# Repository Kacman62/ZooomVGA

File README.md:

# ZooomVGA
An STM32 dev board complete with VGA out

# The Idea

I've been spending a lot of time on software recently and I wanted to do another hardware project. After browsing the Hack CLub slack, I saw there was a zoom call for Blueprint, the hardware program and I decided to join in. The theme was a Trace Race, where you try to make a board in the shortest amount of time. Just an hour before I saw a [VGA library](https://github.com/RoCorbera/BlueVGA) for the exact same STM32 module in the challenge and I knew what my proejct was going to be. The schematic was pretty quick to put together, using a USB C port, an ASM power regulator, the STM32F103C8, a Crystal Oscillator and the VGA port. After getting it reviewed by Kai, and improving it a little bit I moved onto the board in about an hour and a half. The board was a little harder, the VGA port is bigger than the width of a breadboard so I had to flange it out a little. But after aligning everything I started routing the pins. This was a lot harder, I put the MCU off center to get both the USB lines and the crystal to be close to it, but this caused the left side to be very cramped and a pain to route. After 2 hours of painful routing, and another half hour of polish, I finished the entire board in 4 hours. I decided on the name ZooomVGA because this is the fastest I've designed a project, and it was created mainly on the Zoom call.

# The rest of the Owl

I then created a Logo for the board, imporoved the silkscreen, added my logo and exported it to JLCPCB, coming in at around $15 with the stencil and shipping. 
While making the BOM i noticed a slight error with the VGA port, so I changed it to a female connector, did some minor rerouting and fixed the error. The rest of the components are from JLCPCB and cost $20, for a $35 total (slightly lower for me, becuase I ahve LEDS, Resistors, and Capacitors, but should be very similar for you)

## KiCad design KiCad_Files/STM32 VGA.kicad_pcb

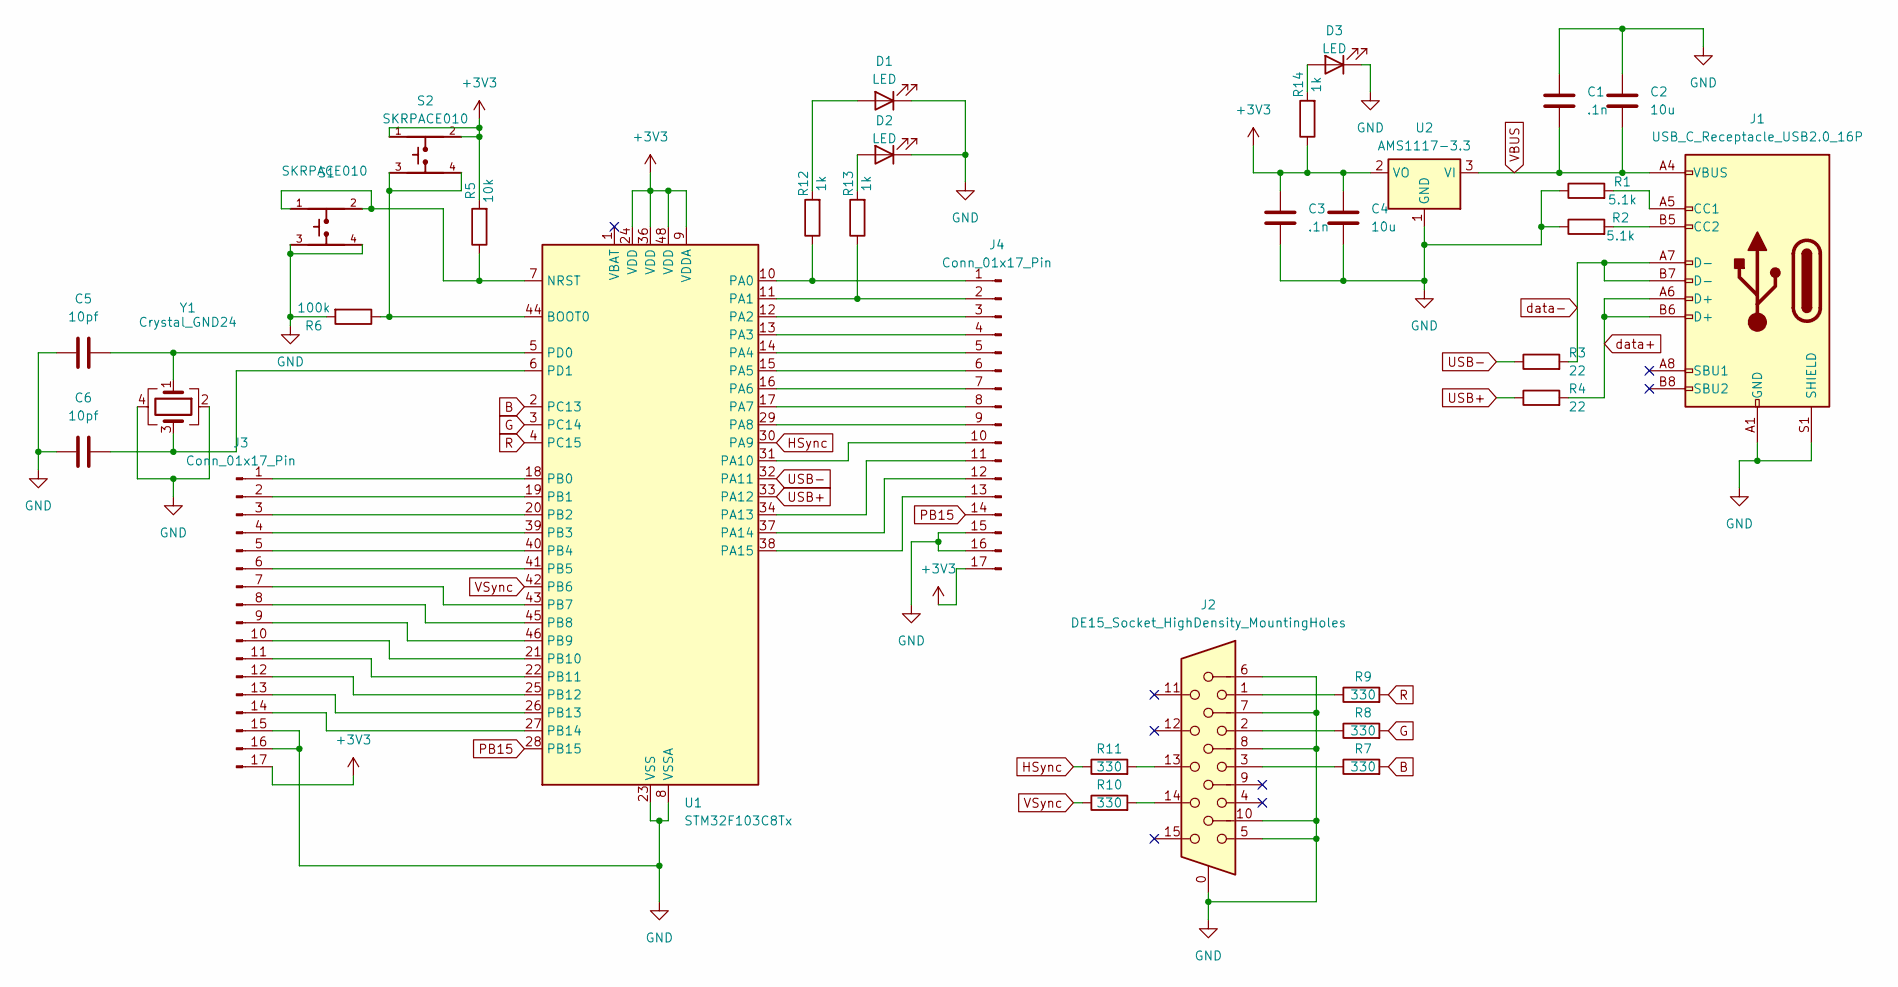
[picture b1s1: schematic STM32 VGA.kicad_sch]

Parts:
C1, C3: .1n; C_0603_1608Metric
C2, C4: 10u; C_0603_1608Metric
C5, C6: 10pf; C_0603_1608Metric
D1, D2, D3: LED; LED_0603_1608Metric
J1: USB_C_Receptacle_USB2.0_16P; Edited_HRO_TYPE-C-31-M-12
J2: DE15_Socket_HighDensity_MountingHoles; DSUB-15-HD_Socket_Horizontal_P2.29x1.90mm_EdgePinOffset3.03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
J3, J4: Conn_01x17_Pin; PinSocket_1x17_P2.54mm_Vertical
R1, R2: 5.1k; R_0603_1608Metric
R3, R4: 22; R_0603_1608Metric
R5: 10k; R_0603_1608Metric
R6: 100k; R_0603_1608Metric
R7, R8, R9, R10, R11: 330; R_0603_1608Metric
R12, R13, R14: 1k; R_0603_1608Metric
S1, S2: SKRPACE010; SW_SKRPACE010
U1: STM32F103C8Tx; LQFP-48_7x7mm_P0.5mm
U2: AMS1117-3.3; SOT-223-3_TabPin2
Y1: Crystal_GND24; SMD3225

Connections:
+3V3: C3.1, C4.1, J3.17, J4.17, R5.2, R14.1, S2.1, S2.2, U1.9 (VDDA), U1.24 (VDD), U1.36 (VDD), U1.48 (VDD), U2.2 (VO); also elsewhere on the board
B: R7.2, U1.2 (PC13)
G: R8.2, U1.3 (PC14)
GND: C1.1, C2.1, C3.2, C4.2, C5.1, C6.1, D1.1 (K), D2.1 (K), D3.1 (K), J1.A1 (GND), J1.A12 (GND), J1.B1 (GND), J1.B12 (GND), J1.S1 (SHIELD), J2.0, J2.5, J2.6, J2.7, J2.8, J2.10, J3.15, J3.16, J4.15, J4.16, R1.1, R2.1, R6.2, S1.3, S1.4, U1.8 (VSSA), U1.23 (VSS), U1.35 (VSS), U1.47 (VSS), U2.1 (GND), Y1.2, Y1.4; also elsewhere on the board
HSync: R11.1, U1.30 (PA9)
unnamed: D1.2 (A), R12.2
unnamed: D2.2 (A), R13.2
unnamed: D3.2 (A), R14.2
unnamed: J1.A5 (CC1), R1.2
unnamed: J1.B5 (CC2), R2.2
unnamed: J2.1, R9.1
unnamed: J2.2, R8.1
unnamed: J2.3, R7.1
unnamed: J2.13, R11.2
unnamed: J2.14, R10.2
unnamed: J3.1, U1.18 (PB0)
unnamed: J3.2, U1.19 (PB1)
unnamed: J3.3, U1.20 (PB2)
unnamed: J3.4, U1.39 (PB3)
unnamed: J3.5, U1.40 (PB4)
unnamed: J3.6, U1.41 (PB5)
unnamed: J3.7, U1.43 (PB7)
unnamed: J3.8, U1.45 (PB8)
unnamed: J3.9, U1.46 (PB9)
unnamed: J3.10, U1.21 (PB10)
unnamed: J3.11, U1.22 (PB11)
unnamed: J3.12, U1.25 (PB12)
unnamed: J3.13, U1.26 (PB13)
unnamed: J3.14, U1.27 (PB14)
unnamed: J4.1, R12.1, U1.10 (PA0)
unnamed: J4.2, R13.1, U1.11 (PA1)
unnamed: J4.3, U1.12 (PA2)
unnamed: J4.4, U1.13 (PA3)
unnamed: J4.5, U1.14 (PA4)
unnamed: J4.6, U1.15 (PA5)
unnamed: J4.7, U1.16 (PA6)
unnamed: J4.8, U1.17 (PA7)
unnamed: J4.9, U1.29 (PA8)
unnamed: J4.10, U1.31 (PA10)
unnamed: J4.11, U1.34 (PA13)
unnamed: J4.12, U1.37 (PA14)
unnamed: J4.13, U1.38 (PA15)
unnamed 42: R6.1, S2.3, S2.4, U1.44 (BOOT0); also elsewhere on the board
unnamed 43: R5.1, S1.1, S1.2, U1.7 (NRST); also elsewhere on the board
unnamed: C5.2, U1.5 (PD0), Y1.1
unnamed: C6.2, U1.6 (PD1), Y1.3
PB15: J4.14, U1.28 (PB15)
R: R9.2, U1.4 (PC15)
USB+: R4.1, U1.33 (PA12)
USB-: R3.1, U1.32 (PA11)
VBUS: C1.2, C2.2, J1.A4 (VBUS), J1.A9 (VBUS), J1.B4 (VBUS), J1.B9 (VBUS), U2.3 (VI)
VSync: R10.1, U1.42 (PB6)
data+: J1.A6 (D+), J1.B6 (D+), R4.2
data-: J1.A7 (D-), J1.B7 (D-), R3.2

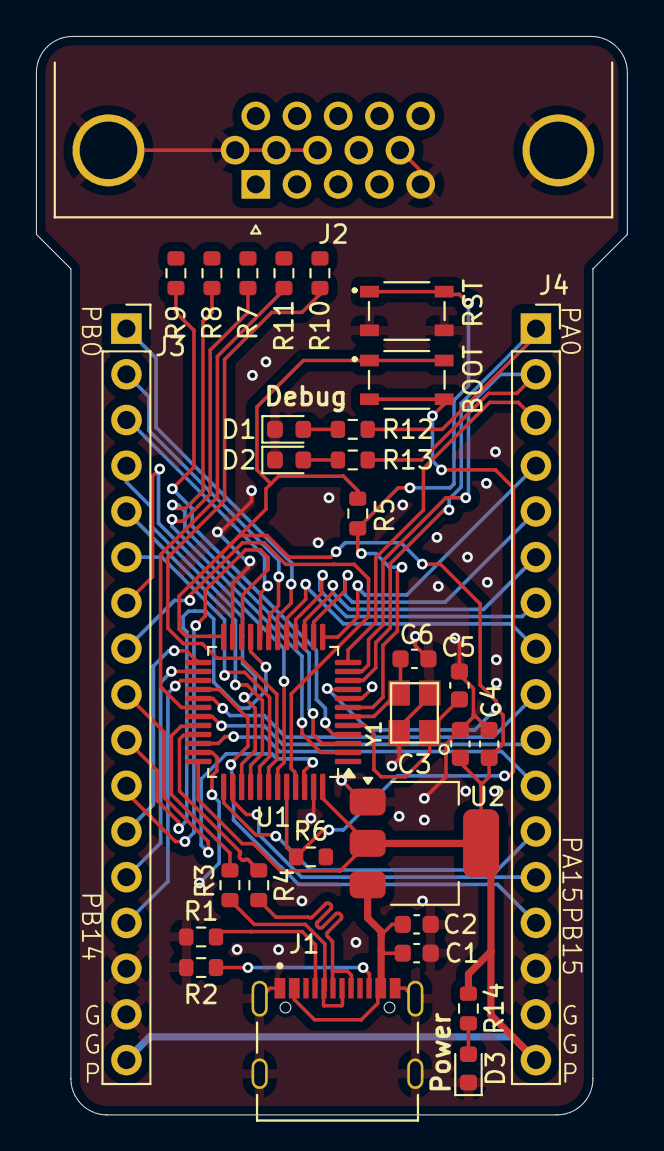
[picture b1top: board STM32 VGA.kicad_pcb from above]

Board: 2 copper layers, 32.8 x 59.9 mm, 32 parts (0 on the bottom side), 54 nets.

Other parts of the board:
BOOT: SKRPACE010; SW_SKRPACE010
RST: SKRPACE010; SW_SKRPACE010

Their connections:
+3V3: BOOT.1, BOOT.2; also elsewhere on the board
GND: RST.3, RST.4; also elsewhere on the board
unnamed 42: BOOT.3, BOOT.4; also elsewhere on the board
unnamed 43: RST.1, RST.2; also elsewhere on the board

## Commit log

2025-11-23 Add project idea and development process to README
    Expanded the README to include project background and details.
2025-11-23 Update README with VGA port correction details
    Corrected the VGA port to a female connector and made minor rerouting adjustments.
2025-11-23 Update README with VGA library link
    Added a link to the VGA library used in the project description.
2026-01-01 Add new image to README
    Added a new image to the README file.
2026-01-01 Updated to V1.2 Schematics and PCB
